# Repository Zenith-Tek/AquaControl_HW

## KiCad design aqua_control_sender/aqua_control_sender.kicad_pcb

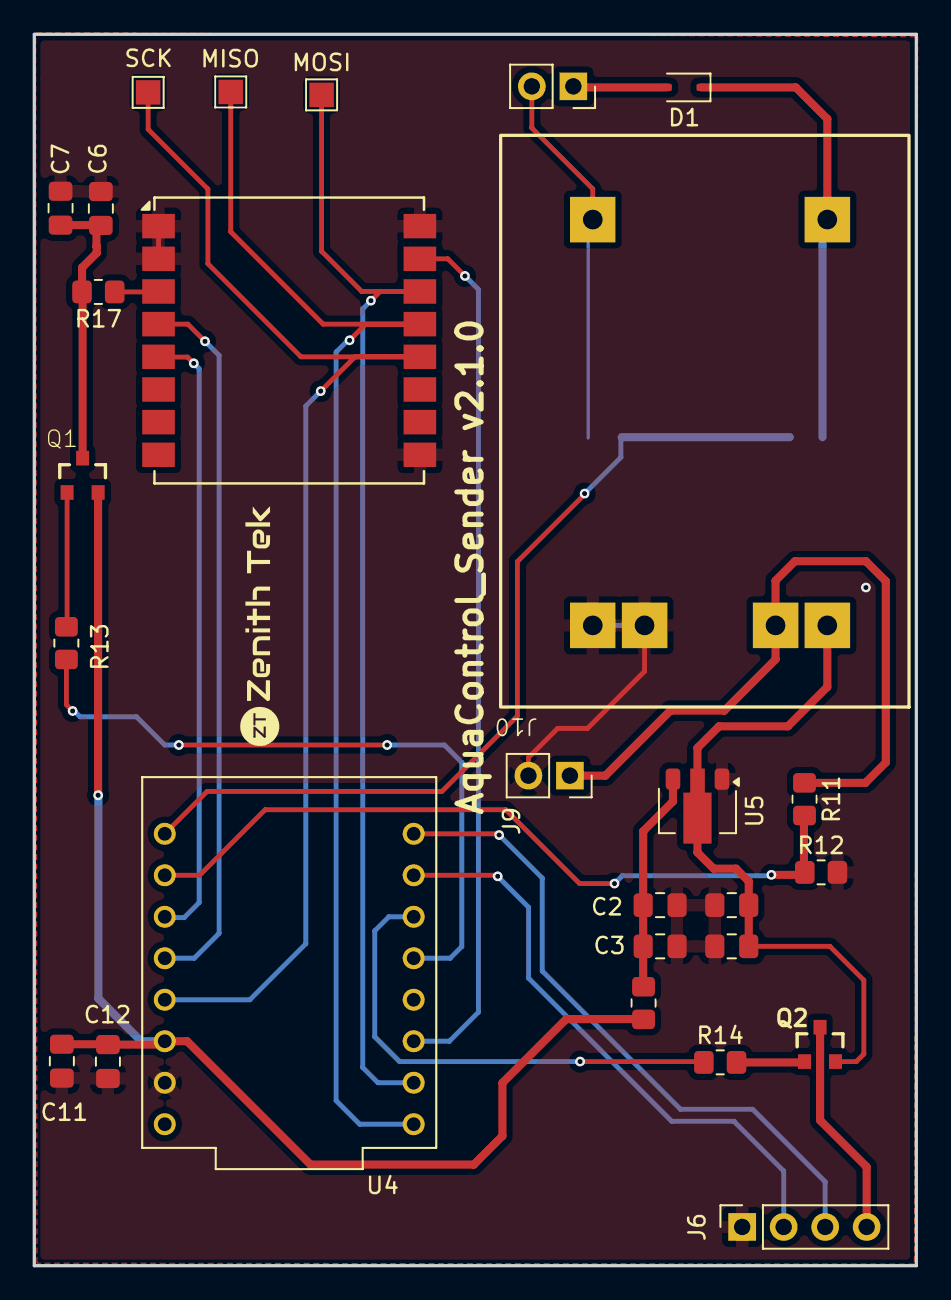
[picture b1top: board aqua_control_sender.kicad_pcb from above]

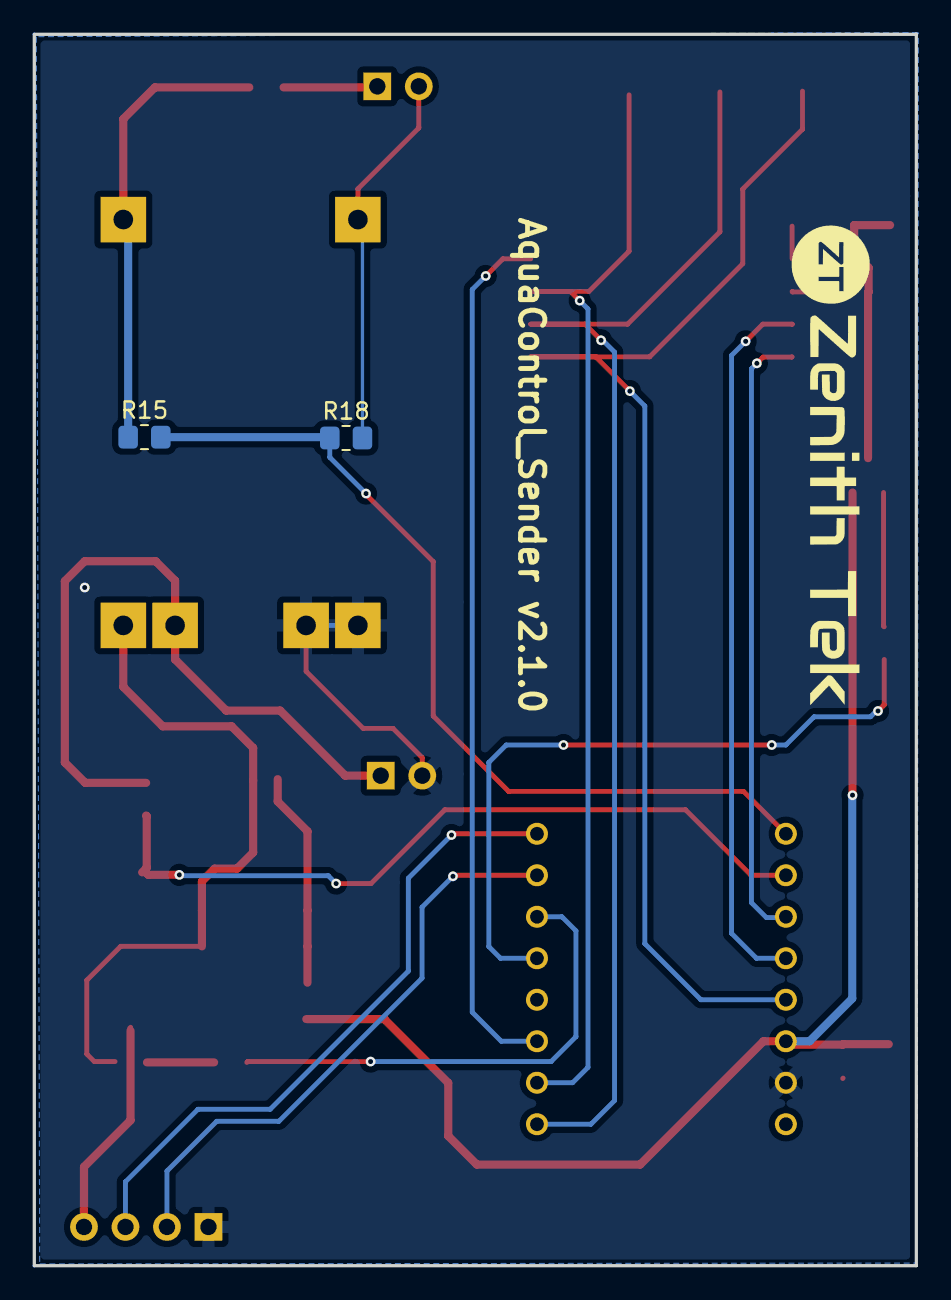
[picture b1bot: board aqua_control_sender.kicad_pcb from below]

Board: 2 copper layers, 54.0 x 75.4 mm, 29 parts (2 on the bottom side), 25 nets.

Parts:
C1, C2, C6, C11: 100nf; C_0805_2012Metric_Pad1.18x1.45mm_HandSolder
C3, C10: 10uf/16v; C_0805_2012Metric_Pad1.18x1.45mm_HandSolder
C7: 10uf; C_0805_2012Metric_Pad1.18x1.45mm_HandSolder
C12: 47nf; C_0805_2012Metric_Pad1.18x1.45mm_HandSolder
D1: 1N5819WS; D_SOD-323
J6: PinSocket_1x04_P2.54mm_Vertical
J8, J9: PinSocket_1x02_P2.54mm_Vertical
J10: TP4056
MISO: TestPoint; TestPoint_Pad_1.5x1.5mm
MOSI: TestPoint; TestPoint_Pad_1.5x1.5mm
Q1, Q2: AO3401A; SOT23-3
R11, R12, R15, R18: 100k; R_0805_2012Metric_Pad1.20x1.40mm_HandSolder
R13, R14: 1k; R_0805_2012Metric_Pad1.20x1.40mm_HandSolder
R16, R17: 0E; R_0805_2012Metric_Pad1.20x1.40mm_HandSolder
SCK: TestPoint; TestPoint_Pad_1.5x1.5mm
U3: RA-02_LORA; Ai-Thinker-Ra-01-LoRa
U4: ESP32-C3_SUPERMINI_TH; MODULE_ESP32-C3_SUPERMINI_TH
U5: MCP1700x-120xxMB; SOT-89-3

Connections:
3.3v: C11.1, C12.1, Q1.2, R16.1, U4.3.3 (3V3)
BAT+: J9.1, J10.2, R11.1
BAT_IN: R11.2, R12.1, U4.1 (GPIO1)
DIO0: U3.5 (DI00), U4.2 (GPIO2)
GND: C1.2, C2.2, C3.2, C6.1, C7.1, C10.2, C11.2, C12.2, J6.1, J9.2, J10.3, J10.4, R12.2, U3.1 (GND), U3.2 (GND), U3.9 (GND), U3.16 (GND), U4.G (GND), U5.1 (GND)
JSN_OUT: J6.4, Q2.3
JSN_PWR: R14.1, U4.10 (GPIO10)
LORA_OUT: C6.2, C7.2, Q1.3, R17.2
LORA_PWR: R13.1, U4.9 (GPIO9)
MISO: MISO.1 (1_1), U3.13 (MISO), U4.5 (GPIO5)
MOSI: MOSI.1 (1_1), U3.14 (MOSI), U4.6 (GPIO6)
NSS: U3.15 (NSS), U4.7 (GPIO7)
unnamed: Q1.1, R13.2
unnamed: Q2.1, R14.2
unnamed: R17.1, U3.3 (3.3V)
unnamed: C2.1, C3.1, R16.2, U5.3 (VO)
RST: U3.4 (RESET), U4.3 (GPIO3)
RX_TRIG: J6.3, U4.21 (GPIO21)
SCK: SCK.1 (1_1), U3.12 (SCK), U4.4 (GPIO4)
SOL_IN: R15.2, R18.1, U4.0 (GPIO0)
SOL_IN+: D1.2 (A), J8.1
SOL_IN-: J8.2, J10.6, R18.2
SOL_PWR+: D1.1 (K), J10.5, R15.1
TX_ECHO: J6.2, U4.20 (GPIO20)
VBAT: C1.1, C10.1, J10.1, Q2.2, U5.2 (VI)

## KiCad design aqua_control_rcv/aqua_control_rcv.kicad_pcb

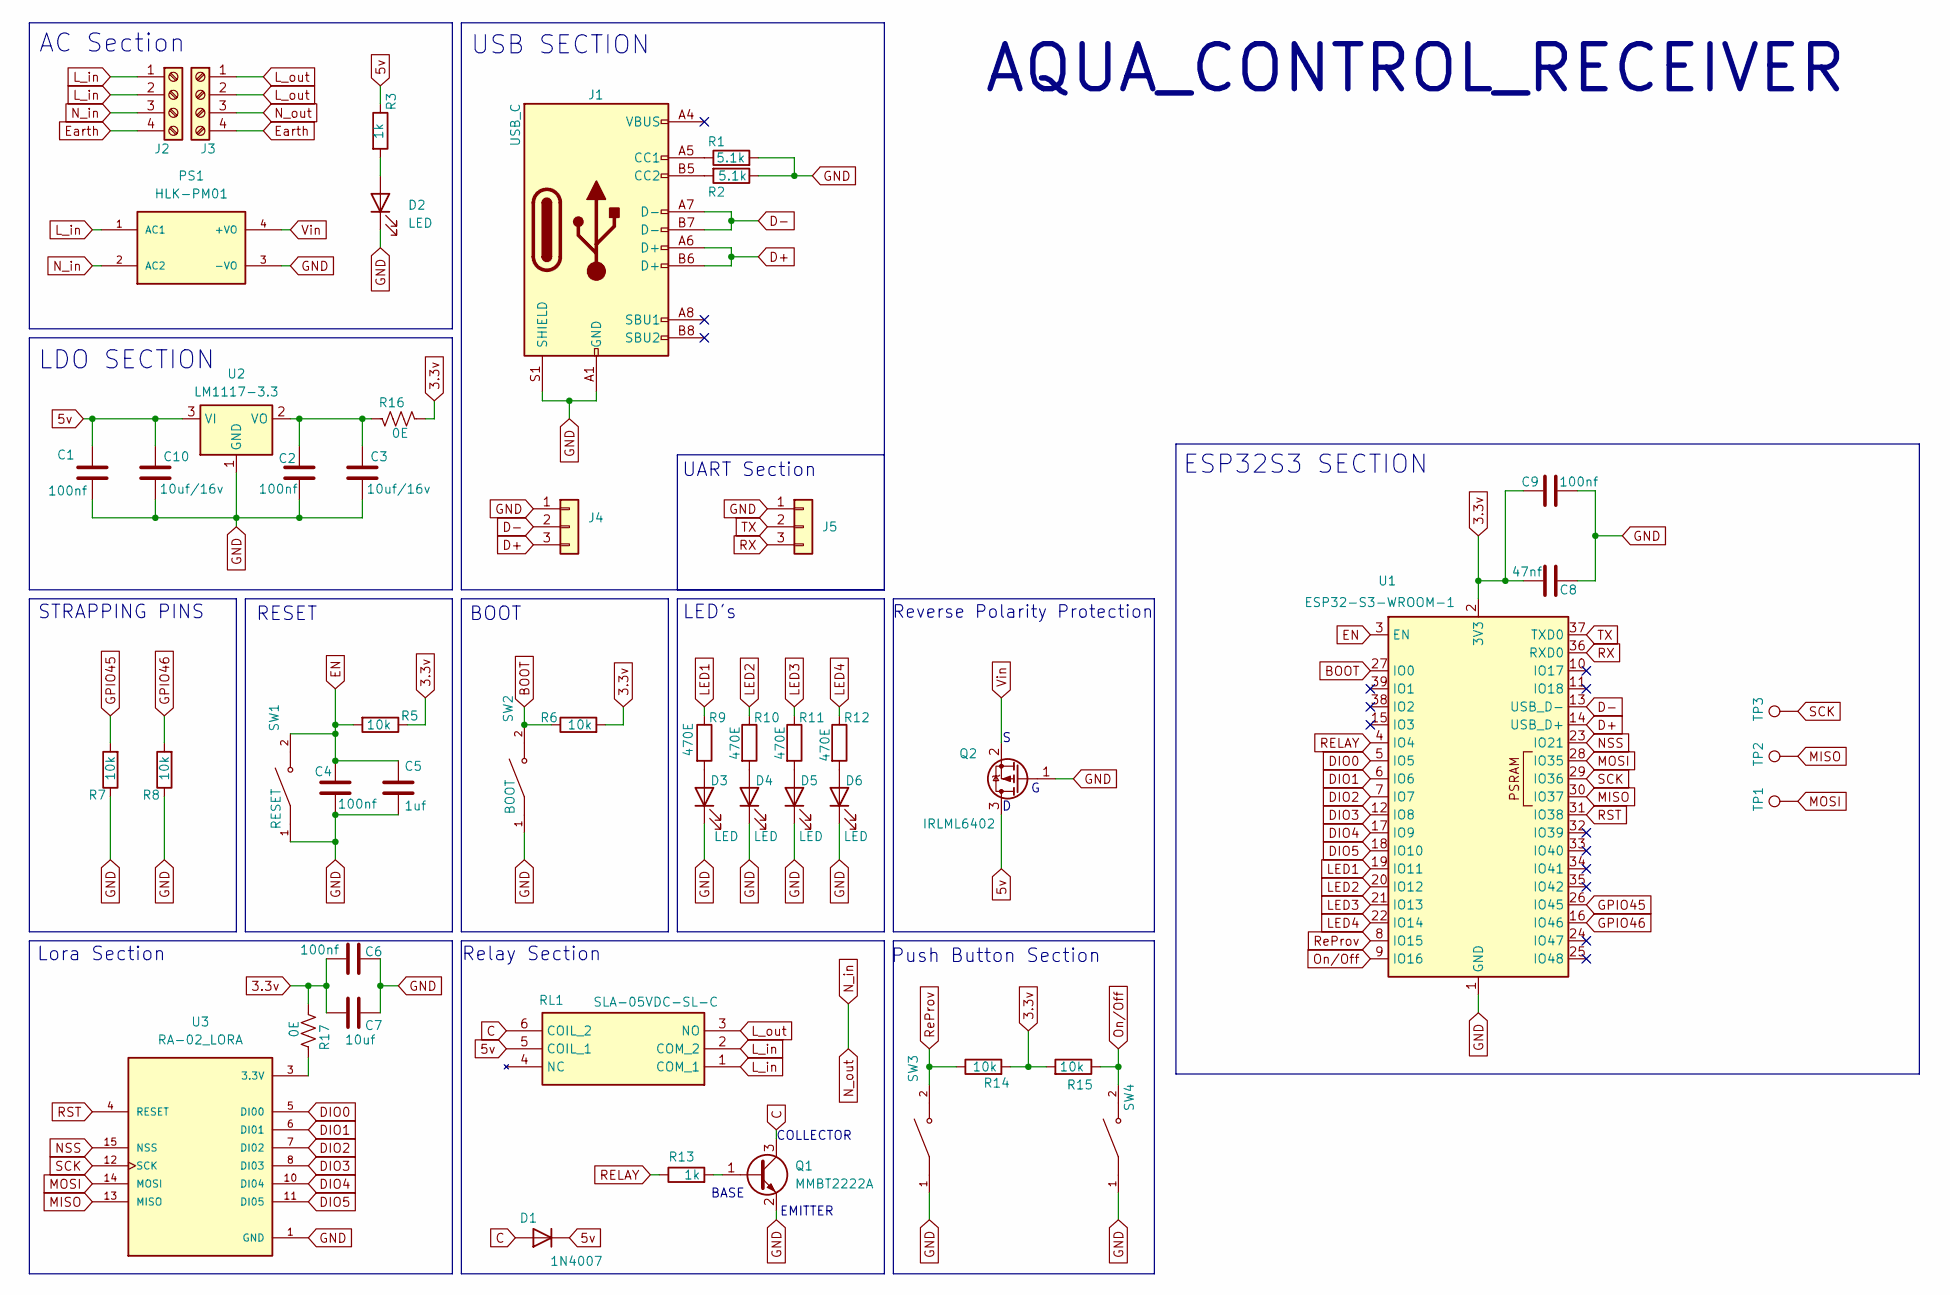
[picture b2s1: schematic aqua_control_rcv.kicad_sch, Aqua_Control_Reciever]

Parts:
C1, C2, C4, C6, C9: 100nf; C_0805_2012Metric_Pad1.18x1.45mm_HandSolder
C3, C10: 10uf/16v; C_0805_2012Metric_Pad1.18x1.45mm_HandSolder
C5: 1uf; C_0805_2012Metric_Pad1.18x1.45mm_HandSolder
C7: 10uf; C_0805_2012Metric_Pad1.18x1.45mm_HandSolder
C8: 47nf; C_0805_2012Metric_Pad1.18x1.45mm_HandSolder
D1: 1N4007; D_SMA
D2, D3, D4, D5, D6: LED; LED_1206_3216Metric_Pad1.42x1.75mm_HandSolder
J1: USB_C; USB_C_Receptacle_JAE_DX07S016JA1R1500
J2, J3: Screw_Terminal_01x04; TerminalBlock_MaiXu_MX126-5.0-04P_1x04_P5.00mm
J4, J5: Conn_01x03; PinSocket_1x03_P2.54mm_Vertical
PS1: HLK-PM01; CONV_HLK-PM01
Q1: MMBT2222A; SOT-23
Q2: IRLML6402; SOT-23
R1, R2: 5.1k; R_0805_2012Metric_Pad1.20x1.40mm_HandSolder
R3, R13: 1k; R_0805_2012Metric_Pad1.20x1.40mm_HandSolder
R5, R6, R7, R8, R14, R15: 10k; R_0805_2012Metric_Pad1.20x1.40mm_HandSolder
R9, R10, R11, R12: 470E; R_0805_2012Metric_Pad1.20x1.40mm_HandSolder
R16, R17: 0E; R_0805_2012Metric_Pad1.20x1.40mm_HandSolder
RL1: SLA-05VDC-SL-C; SLA05VDCSLC; Manufacturer_Part_Number SLA-05VDC-SL-C
SW1: RESET; SW_TS09-63-25-WT-160-SMT-TR; PARTREV 1.0
SW2, SW3, SW4: BOOT; SW_TS09-63-25-WT-160-SMT-TR; PARTREV 1.0
TP1, TP2, TP3: TestPoint; TestPoint_Pad_1.5x1.5mm
U1: ESP32-S3-WROOM-1
U2: LM1117-3.3; SOT-223-3_TabPin2
U3: RA-02_LORA; Ai-Thinker-Ra-01-LoRa; PARTREV 2018/03/02

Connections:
3.3v: C6.2, C7.2, C8.1, C9.1, R5.1, R6.2, R14.2, R15.2, R16.2, R17.2, U1.2 (3V3)
5v: C1.1, C10.1, D1.1 (K), Q2.3 (D), R3.1, RL1.5 (COIL_1), U2.3 (VI)
BOOT: R6.1, SW2.2, U1.27 (IO0)
C: D1.2 (A), Q1.3 (C), RL1.6 (COIL_2)
D+: J1.A6 (D+), J1.B6 (D+), J4.3, U1.14 (USB_D+)
D-: J1.A7 (D-), J1.B7 (D-), J4.2, U1.13 (USB_D-)
DIO0: U1.5 (IO5), U3.5 (DI00)
DIO1: U1.6 (IO6), U3.6 (DI01)
DIO2: U1.7 (IO7), U3.7 (DI02)
DIO3: U1.12 (IO8), U3.8 (DI03)
DIO4: U1.17 (IO9), U3.10 (DI04)
DIO5: U1.18 (IO10), U3.11 (DI05)
EN: C4.1, C5.1, R5.2, SW1.2, U1.3 (EN)
Earth: J2.4, J3.4
GND: C1.2, C2.2, C3.2, C4.2, C5.2, C6.1, C7.1, C8.2, C9.2, C10.2, D2.1 (K), D3.1 (K), D4.1 (K), D5.1 (K), D6.1 (K), J1.A1 (GND), J1.A12 (GND), J1.B1 (GND), J1.B12 (GND), J1.S1 (SHIELD), J4.1, J5.1, PS1.3 (-VO), Q1.2 (E), Q2.1 (G), R1.2, R2.1, R7.1, R8.1, SW1.1, SW2.1, SW3.1, SW4.1, U1.1 (GND), U1.40 (GND), U1.41 (GND), U2.1 (GND), U3.1 (GND), U3.2 (GND), U3.9 (GND), U3.16 (GND)
GPIO45: R7.2, U1.26 (IO45)
GPIO46: R8.2, U1.16 (IO46)
LED1: R9.1, U1.19 (IO11)
LED2: R10.1, U1.20 (IO12)
LED3: R11.1, U1.21 (IO13)
LED4: R12.1, U1.22 (IO14)
L_in: J2.1, J2.2, PS1.1 (AC1), RL1.1 (COM_1), RL1.2 (COM_2)
L_out: J3.1, J3.2, RL1.3 (NO)
MISO: TP2.1 (1_1), U1.30 (IO37), U3.13 (MISO)
MOSI: TP1.1 (1_1), U1.28 (IO35), U3.14 (MOSI)
NSS: U1.23 (IO21), U3.15 (NSS)
N_in: J2.3, J3.3, PS1.2 (AC2)
unnamed: D2.2 (A), R3.2
unnamed: D3.2 (A), R9.2
unnamed: D4.2 (A), R10.2
unnamed: D5.2 (A), R11.2
unnamed: D6.2 (A), R12.2
unnamed: J1.A5 (CC1), R1.1
unnamed: J1.B5 (CC2), R2.2
unnamed: Q1.1 (B), R13.2
unnamed: C2.1, C3.1, R16.1, U2.2 (VO)
unnamed: R17.1, U3.3 (3.3V)
On/Off: R15.1, SW4.2, U1.9 (IO16)
RELAY: R13.1, U1.4 (IO4)
RST: U1.31 (IO38), U3.4 (RESET)
RX: J5.3, U1.36 (RXD0)
ReProv: R14.1, SW3.2, U1.8 (IO15)
SCK: TP3.1 (1_1), U1.29 (IO36), U3.12 (SCK)
TX: J5.2, U1.37 (TXD0)
Vin: PS1.4 (+VO), Q2.2 (S)

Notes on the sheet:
Push Button Section
Relay Section
STRAPPING PINS
COLLECTOR
Lora Section
Reverse Polarity Protection
LDO SECTION
AQUA_CONTROL_RECEIVER
RESET
BASE
USB SECTION
ESP32S3 SECTION
BOOT
UART Section
AC Section
LED's
EMITTER

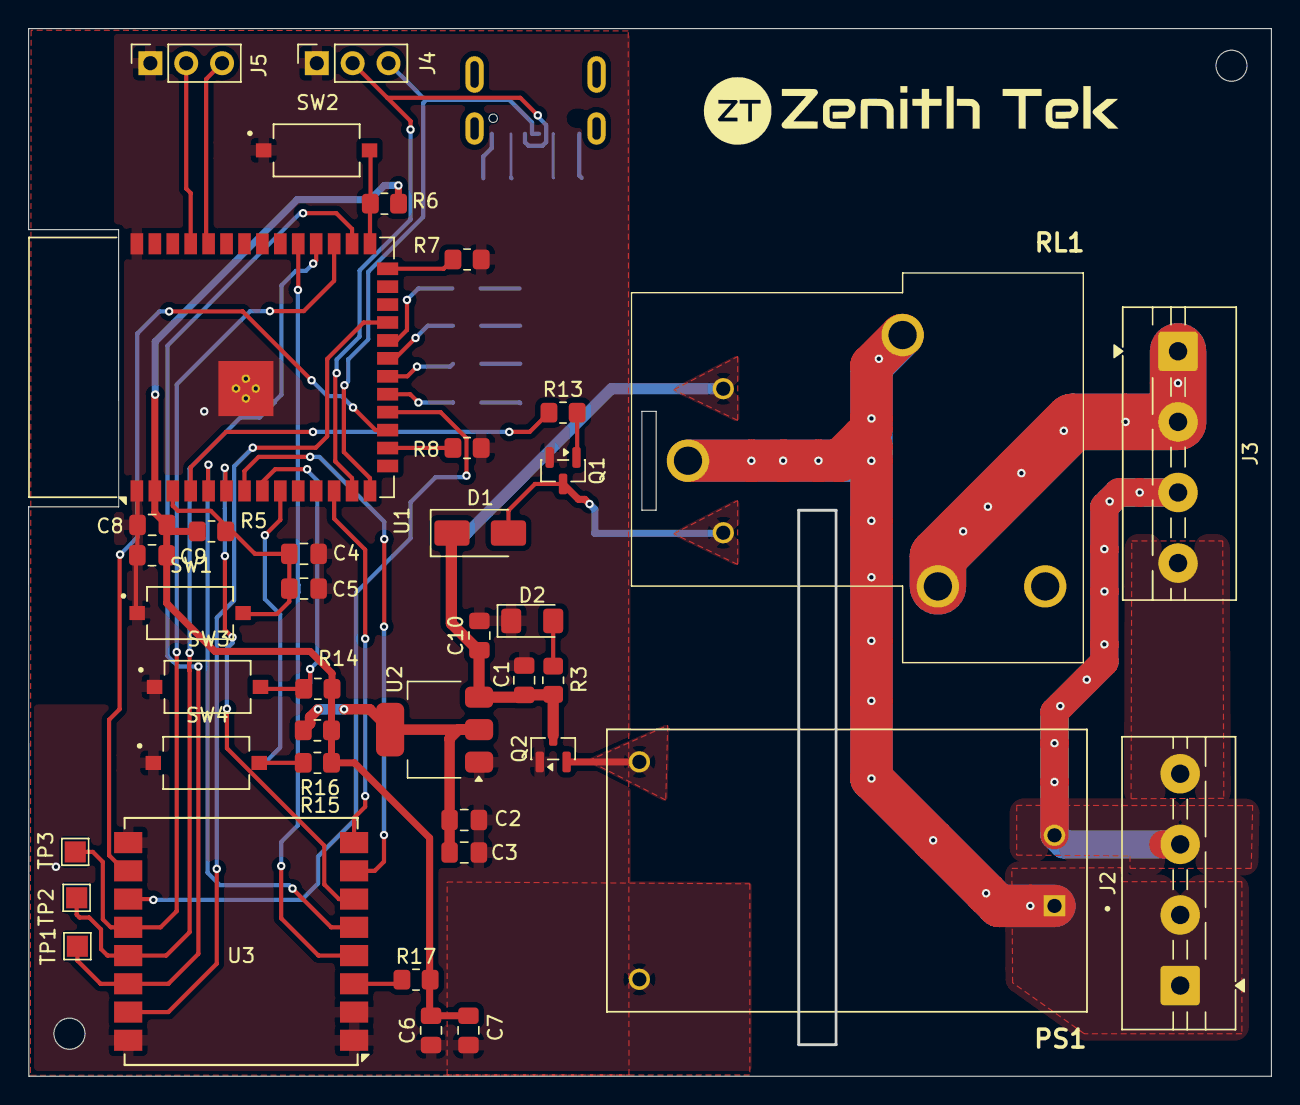
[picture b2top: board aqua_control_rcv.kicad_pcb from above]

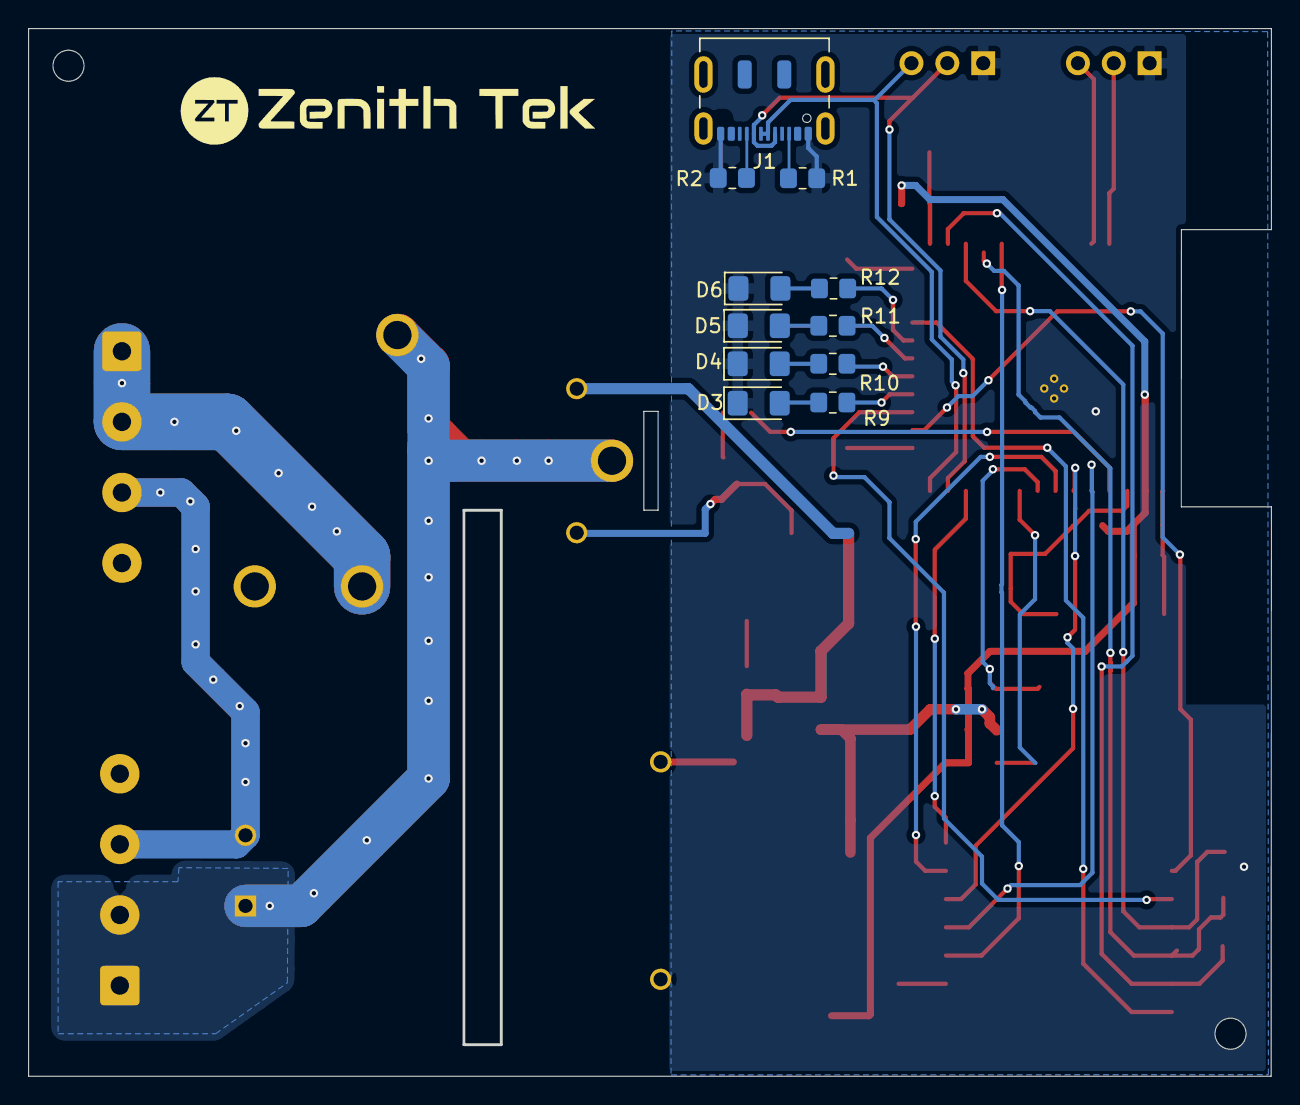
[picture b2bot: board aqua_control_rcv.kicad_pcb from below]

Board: 2 copper layers, 87.9 x 74.0 mm, 51 parts (11 on the bottom side), 45 nets.

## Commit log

2026-06-17 second commit
2026-06-18 added libraries
2026-06-18 routing completed
2026-06-18 completed routing and added logo
2026-06-19 receiver board complete
2026-06-19 sender board complete
2026-06-19 receiver board
2026-06-19 sender board
2026-06-19 final version
2026-06-19 added library
2026-06-19 added history
